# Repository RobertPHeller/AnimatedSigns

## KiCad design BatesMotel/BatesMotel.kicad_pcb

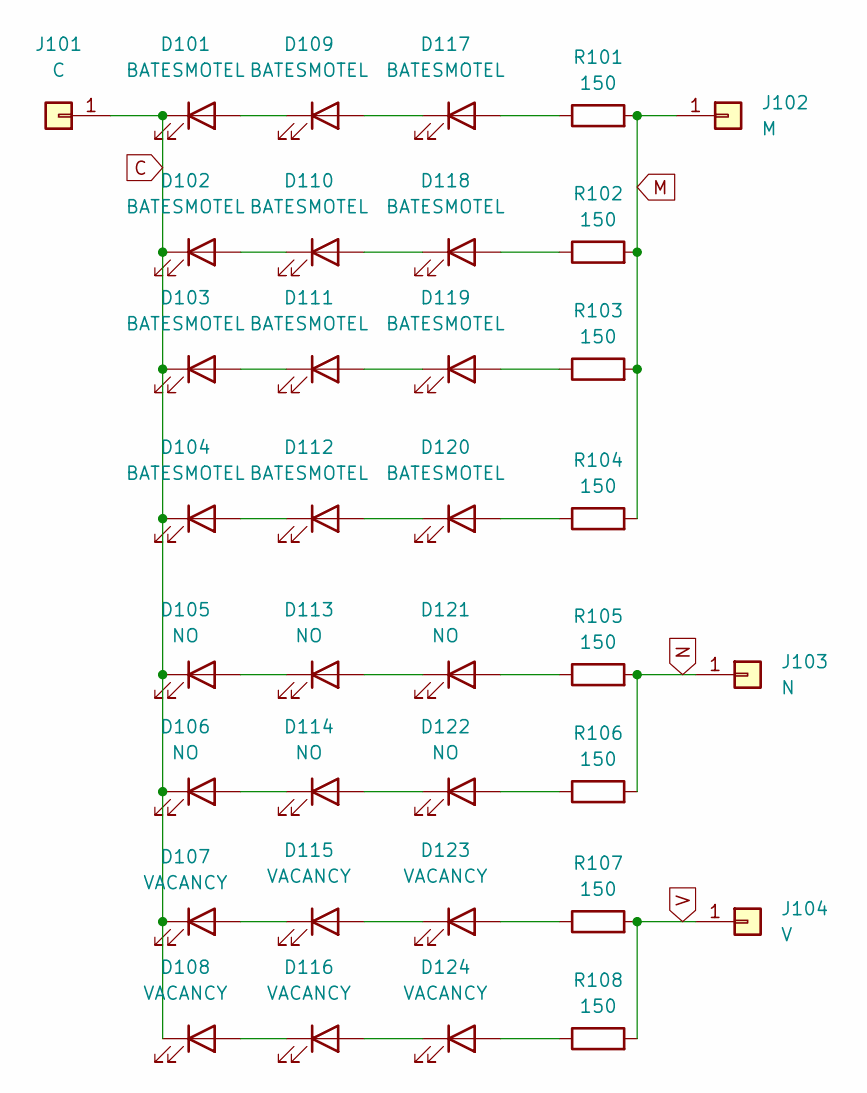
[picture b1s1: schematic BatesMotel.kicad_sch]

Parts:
D101, D102, D103, D104, D109, D110, D111, D112, D117, D118, D119, D120: BATESMOTEL; LED_1206_3216Metric; Mouser Part Number 743-S126AT5UW
D105, D106, D113, D114, D121, D122: NO; LED_0603_1608Metric; Mouser Part Number 630-HSMW-C191-U0000
D107, D108, D115, D116, D123, D124: VACANCY; LED_0603_1608Metric; Mouser Part Number 630-HSMW-C191-U0000
J101: C; ContactPad
J102: M; ContactPad
J103: N; ContactPad
J104: V; ContactPad
R101, R102, R103, R104, R105, R106, R107, R108: 150; R_0603_1608Metric; Mouser Part Number 603-RT0603FRE13150RL

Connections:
C: D101.1 (K), D102.1 (K), D103.1 (K), D104.1 (K), D105.1 (K), D106.1 (K), D107.1 (K), D108.1 (K), J101.1
M: J102.1, R101.2, R102.2, R103.2, R104.2
N: J103.1, R105.2, R106.2
unnamed: D101.2 (A), D109.1 (K)
unnamed: D102.2 (A), D110.1 (K)
unnamed: D103.2 (A), D111.1 (K)
unnamed: D104.2 (A), D112.1 (K)
unnamed: D105.2 (A), D113.1 (K)
unnamed: D106.2 (A), D114.1 (K)
unnamed: D107.2 (A), D115.1 (K)
unnamed: D108.2 (A), D116.1 (K)
unnamed: D109.2 (A), D117.1 (K)
unnamed: D110.2 (A), D118.1 (K)
unnamed: D111.2 (A), D119.1 (K)
unnamed: D112.2 (A), D120.1 (K)
unnamed: D113.2 (A), D121.1 (K)
unnamed: D114.2 (A), D122.1 (K)
unnamed: D115.2 (A), D123.1 (K)
unnamed: D116.2 (A), D124.1 (K)
unnamed: D117.2 (A), R101.1
unnamed: D118.2 (A), R102.1
unnamed: D119.2 (A), R103.1
unnamed: D120.2 (A), R104.1
unnamed: D121.2 (A), R105.1
unnamed: D122.2 (A), R106.1
unnamed: D123.2 (A), R107.1
unnamed: D124.2 (A), R108.1
V: J104.1, R107.2, R108.2

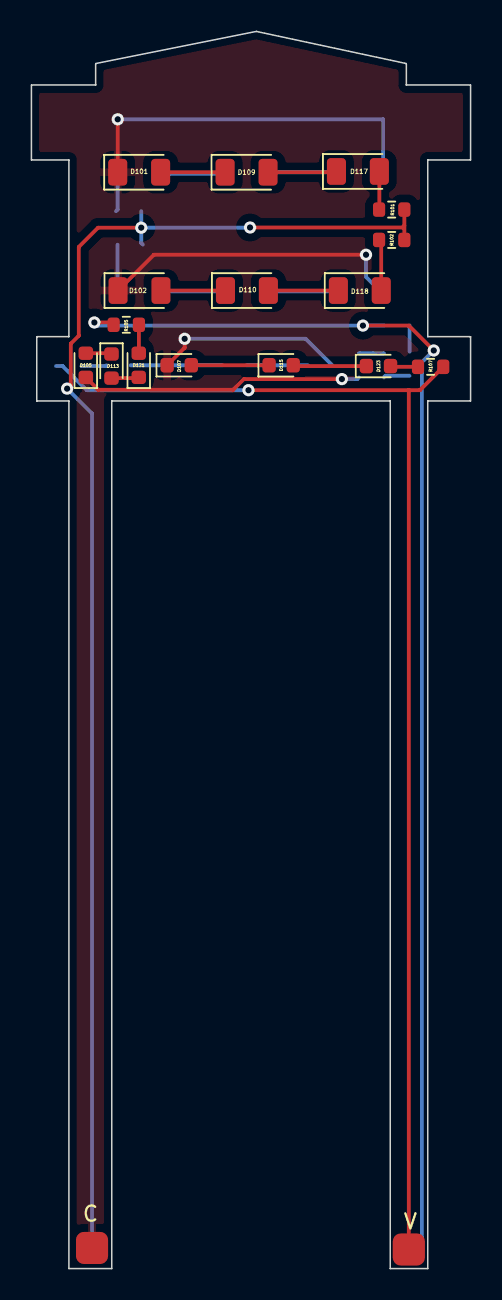
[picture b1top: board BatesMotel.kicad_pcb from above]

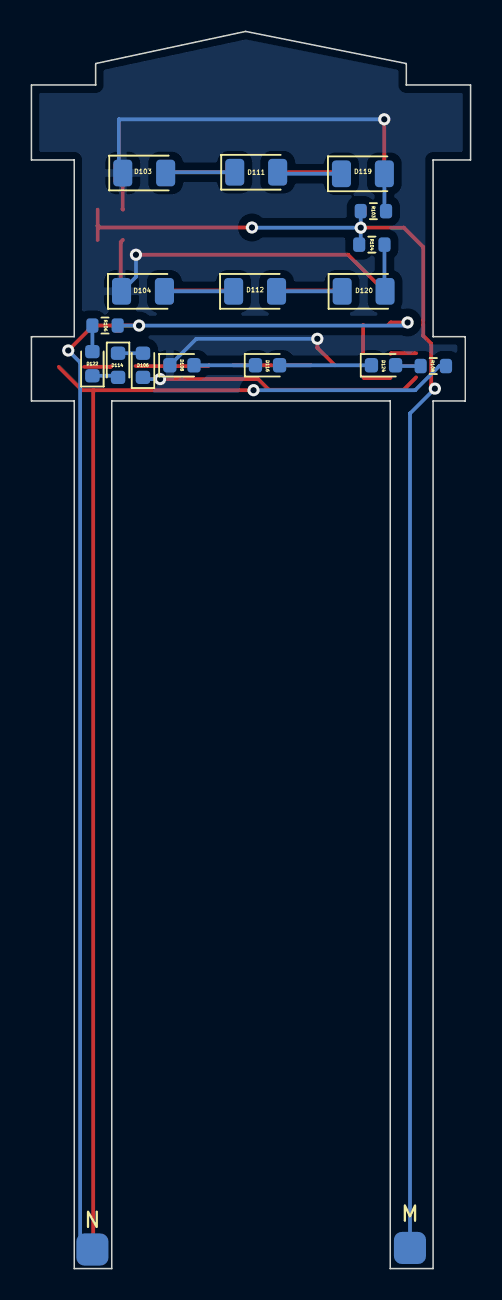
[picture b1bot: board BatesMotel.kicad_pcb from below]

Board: 2 copper layers, 28.7 x 80.7 mm, 36 parts (18 on the bottom side), 28 nets.

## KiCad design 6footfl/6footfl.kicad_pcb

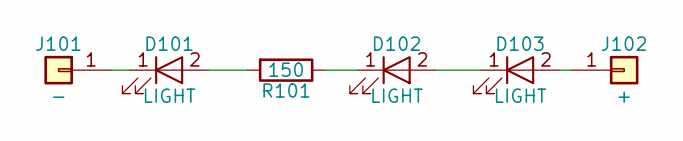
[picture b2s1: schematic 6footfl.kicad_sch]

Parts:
D101, D102, D103: LIGHT; LED_0603; Mouser Part Number 630-HSMW-C191-U0000
J101: -; SmallPad
J102: +; SmallPad
R101: 150; R_0603; Mouser Part Number 603-RT0603FRE13150RL

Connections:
unnamed: D101.1 (K), J101.1
unnamed: D101.2 (A), R101.2
unnamed: D102.1 (K), R101.1
unnamed: D102.2 (A), D103.1 (K)
unnamed: D103.2 (A), J102.1

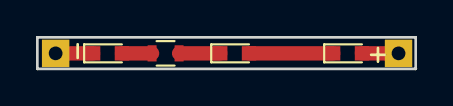
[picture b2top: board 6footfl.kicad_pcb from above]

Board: 2 copper layers, 21.0 x 1.8 mm, 6 parts (0 on the bottom side), 5 nets.

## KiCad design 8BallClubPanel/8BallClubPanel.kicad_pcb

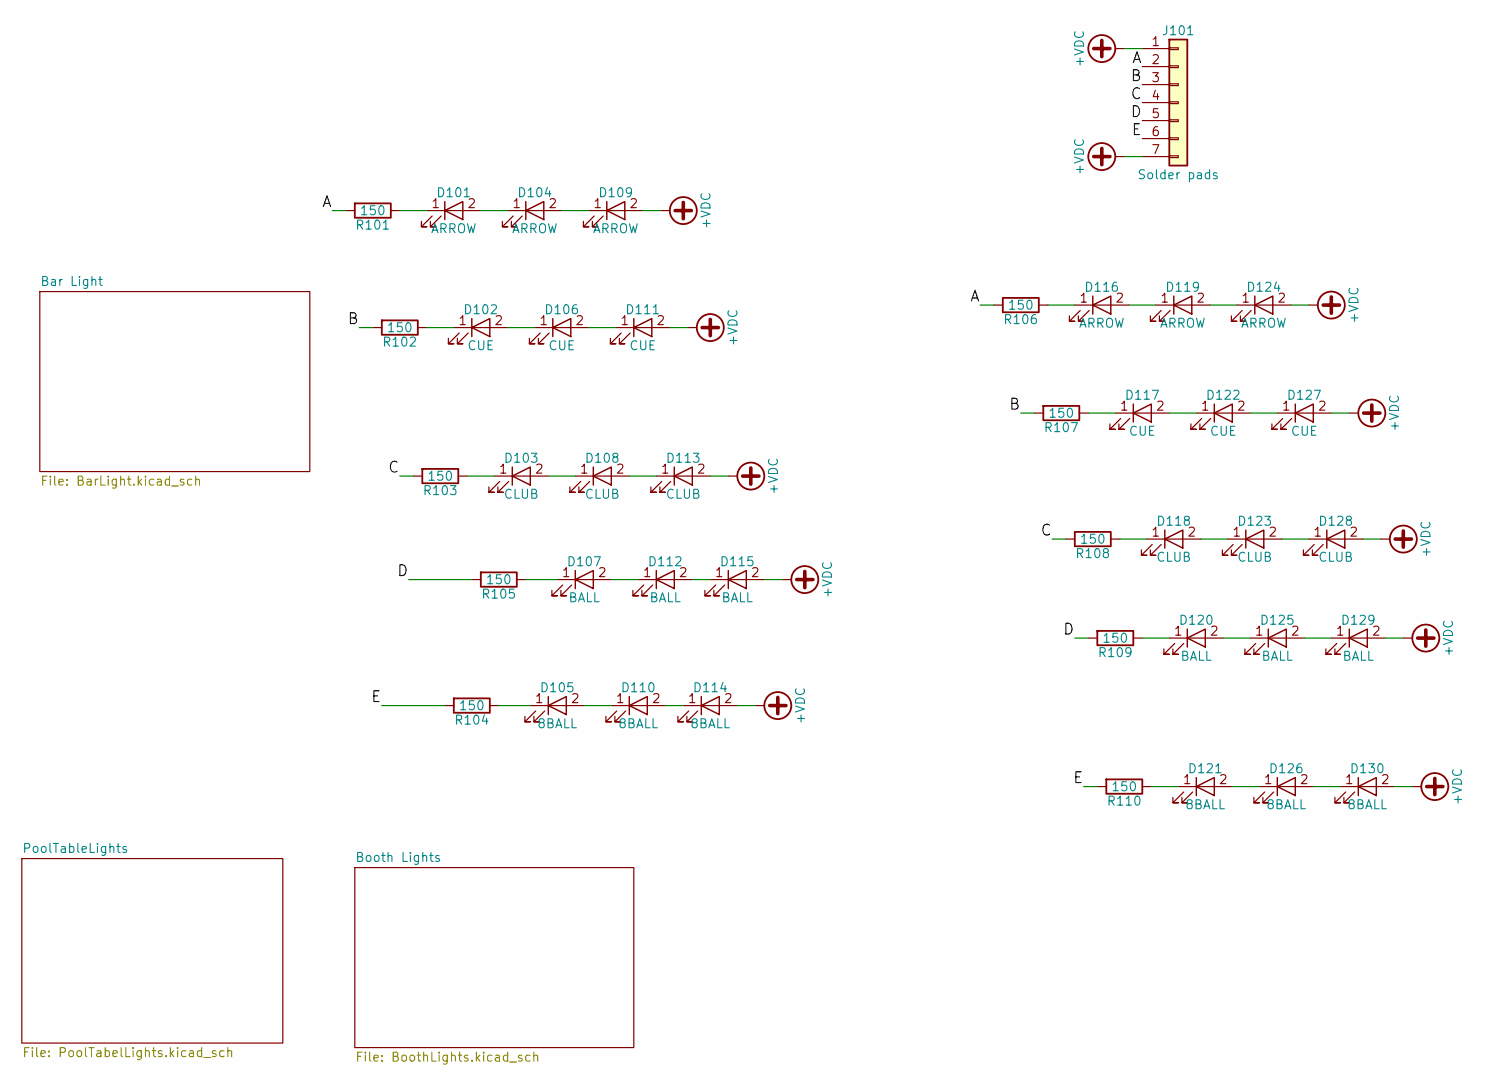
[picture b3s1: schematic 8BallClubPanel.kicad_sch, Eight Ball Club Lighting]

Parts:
D101, D104, D109, D116, D119, D124: ARROW; LED_1206_3216Metric; Mouser Part Number 743-S126AT5UW
D102, D106, D111, D117, D122, D127: CUE; LED_1206_3216Metric; Mouser Part Number 743-S126AT5UW
D103, D108, D113, D118, D123, D128: CLUB; LED_1206_3216Metric; Mouser Part Number 743-S126AT5UW
D105, D110, D114, D121, D126, D130: 8BALL; LED_1206_3216Metric; Mouser Part Number 743-S126AT5UW
D107, D112, D115, D120, D125, D129: BALL; LED_1206_3216Metric; Mouser Part Number 743-S126AT5UW
J101: Solder pads; PowerPlus5X2
R101, R102, R103, R104, R105, R106, R107, R108, R109, R110: 150; R_0603_1608Metric; Mouser Part Number 603-RT0603FRE13150RL

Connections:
+VDC: D109.2 (A), D111.2 (A), D113.2 (A), D114.2 (A), D115.2 (A), D124.2 (A), D127.2 (A), D128.2 (A), D129.2 (A), D130.2 (A), J101.1, J101.7
/A: J101.2, R101.2, R106.2
/B: J101.3, R102.2, R107.2
/C: J101.4, R103.2, R108.2
/D: J101.5, R105.2, R109.2
/E: J101.6, R104.2, R110.2
unnamed: D101.1 (K), R101.1
unnamed: D101.2 (A), D104.1 (K)
unnamed: D102.1 (K), R102.1
unnamed: D102.2 (A), D106.1 (K)
unnamed: D103.1 (K), R103.1
unnamed: D103.2 (A), D108.1 (K)
unnamed: D104.2 (A), D109.1 (K)
unnamed: D105.1 (K), R104.1
unnamed: D105.2 (A), D110.1 (K)
unnamed: D106.2 (A), D111.1 (K)
unnamed: D107.1 (K), R105.1
unnamed: D107.2 (A), D112.1 (K)
unnamed: D108.2 (A), D113.1 (K)
unnamed: D110.2 (A), D114.1 (K)
unnamed: D112.2 (A), D115.1 (K)
unnamed: D116.1 (K), R106.1
unnamed: D116.2 (A), D119.1 (K)
unnamed: D117.1 (K), R107.1
unnamed: D117.2 (A), D122.1 (K)
unnamed: D118.1 (K), R108.1
unnamed: D118.2 (A), D123.1 (K)
unnamed: D119.2 (A), D124.1 (K)
unnamed: D120.1 (K), R109.1
unnamed: D120.2 (A), D125.1 (K)
unnamed: D121.1 (K), R110.1
unnamed: D121.2 (A), D126.1 (K)
unnamed: D122.2 (A), D127.1 (K)
unnamed: D123.2 (A), D128.1 (K)
unnamed: D125.2 (A), D129.1 (K)
unnamed: D126.2 (A), D130.1 (K)

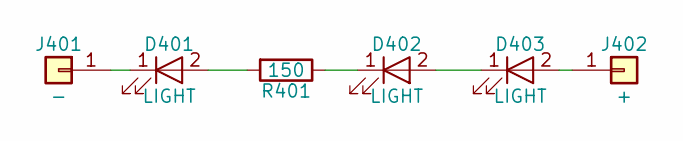
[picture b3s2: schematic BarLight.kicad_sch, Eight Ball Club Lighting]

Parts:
D401, D402, D403: LIGHT; LED_PLCC-2; Mouser Part Number 941-CLM3CWKWCWBYA153
J401: -; TestPoint_THTPad_D3.0mm_Drill1.5mm
J402: +; TestPoint_THTPad_D3.0mm_Drill1.5mm
R401: 150; R_0603_1608Metric; Mouser Part Number 603-RT0603FRE13150RL

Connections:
unnamed: D401.1 (K), J401.1
unnamed: D401.2 (A), R401.2
unnamed: D402.1 (K), R401.1
unnamed: D402.2 (A), D403.1 (K)
unnamed: D403.2 (A), J402.1

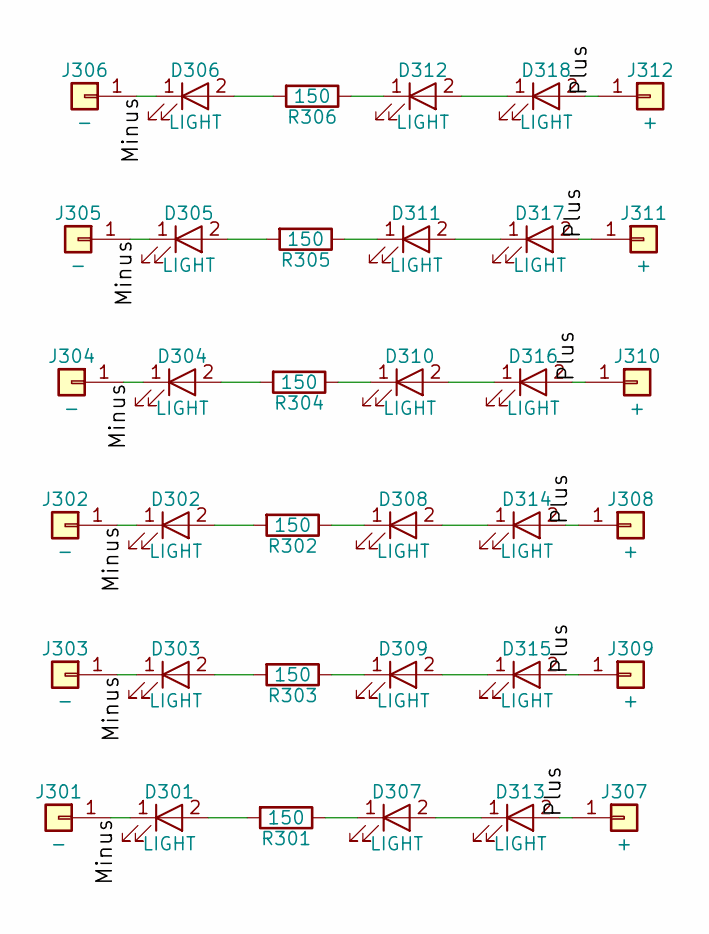
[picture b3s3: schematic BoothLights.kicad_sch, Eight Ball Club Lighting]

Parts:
D301, D302, D303, D304, D305, D306, D307, D308, D309, D310, D311, D312, D313, D314, D315, D316, D317, D318: LIGHT; LED_0402_1005Metric; Mouser Part Number 743-IN-S42ATUW
J301, J302, J303, J304, J305, J306: -; BottomPad
J307, J308, J309, J310, J311, J312: +; BottomPad
R301, R302, R303, R304, R305, R306: 150; R_0402_1005Metric; Mouser Part Number 603-RC0402JR-13150RL

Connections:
/Booth Lights/Minus: D301.1 (K), D302.1 (K), D303.1 (K), D304.1 (K), D305.1 (K), D306.1 (K), J301.1, J302.1, J303.1, J304.1, J305.1, J306.1
/Booth Lights/Plus: D313.2 (A), D314.2 (A), D315.2 (A), D316.2 (A), D317.2 (A), D318.2 (A), J307.1, J308.1, J309.1, J310.1, J311.1, J312.1
unnamed: D301.2 (A), R301.2
unnamed: D302.2 (A), R302.2
unnamed: D303.2 (A), R303.2
unnamed: D304.2 (A), R304.2
unnamed: D305.2 (A), R305.2
unnamed: D306.2 (A), R306.2
unnamed: D307.1 (K), R301.1
unnamed: D307.2 (A), D313.1 (K)
unnamed: D308.1 (K), R302.1
unnamed: D308.2 (A), D314.1 (K)
unnamed: D309.1 (K), R303.1
unnamed: D309.2 (A), D315.1 (K)
unnamed: D310.1 (K), R304.1
unnamed: D310.2 (A), D316.1 (K)
unnamed: D311.1 (K), R305.1
unnamed: D311.2 (A), D317.1 (K)
unnamed: D312.1 (K), R306.1
unnamed: D312.2 (A), D318.1 (K)

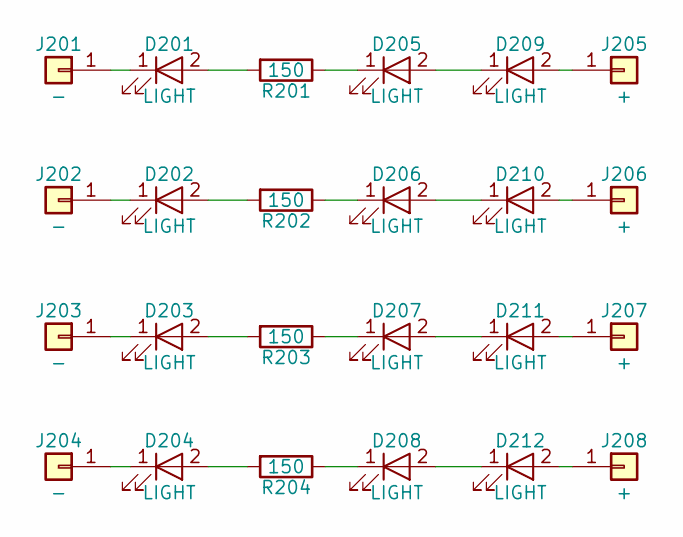
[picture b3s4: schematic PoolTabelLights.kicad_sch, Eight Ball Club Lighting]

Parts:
D201, D202, D203, D204, D205, D206, D207, D208, D209, D210, D211, D212: LIGHT; LED_0603_1608Metric; Mouser Part Number 630-HSMW-C191-U0000
J201, J202, J203, J204: -; SmallPad
J205, J206, J207, J208: +; SmallPad
R201, R202, R203, R204: 150; R_0603_1608Metric; Mouser Part Number 603-RT0603FRE13150RL

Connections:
unnamed: D201.1 (K), J201.1
unnamed: D201.2 (A), R201.2
unnamed: D202.1 (K), J202.1
unnamed: D202.2 (A), R202.2
unnamed: D203.1 (K), J203.1
unnamed: D203.2 (A), R203.2
unnamed: D204.1 (K), J204.1
unnamed: D204.2 (A), R204.2
unnamed: D205.1 (K), R201.1
unnamed: D205.2 (A), D209.1 (K)
unnamed: D206.1 (K), R202.1
unnamed: D206.2 (A), D210.1 (K)
unnamed: D207.1 (K), R203.1
unnamed: D207.2 (A), D211.1 (K)
unnamed: D208.1 (K), R204.1
unnamed: D208.2 (A), D212.1 (K)
unnamed: D209.2 (A), J205.1
unnamed: D210.2 (A), J206.1
unnamed: D211.2 (A), J207.1
unnamed: D212.2 (A), J208.1

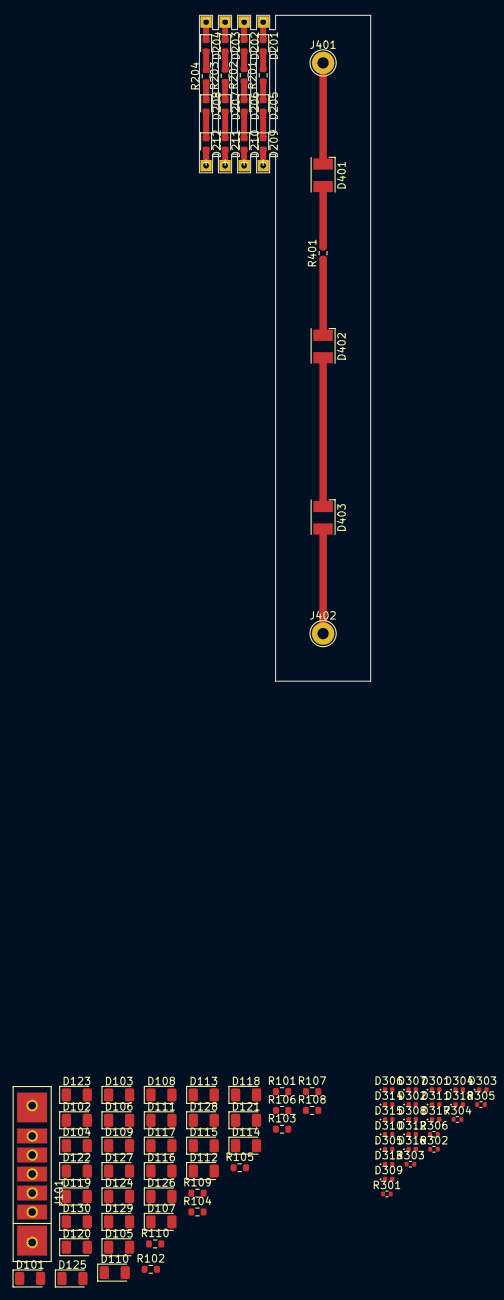
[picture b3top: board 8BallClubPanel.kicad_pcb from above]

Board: 2 copper layers, 22.9 x 88.9 mm, 107 parts (0 on the bottom side), 81 nets.

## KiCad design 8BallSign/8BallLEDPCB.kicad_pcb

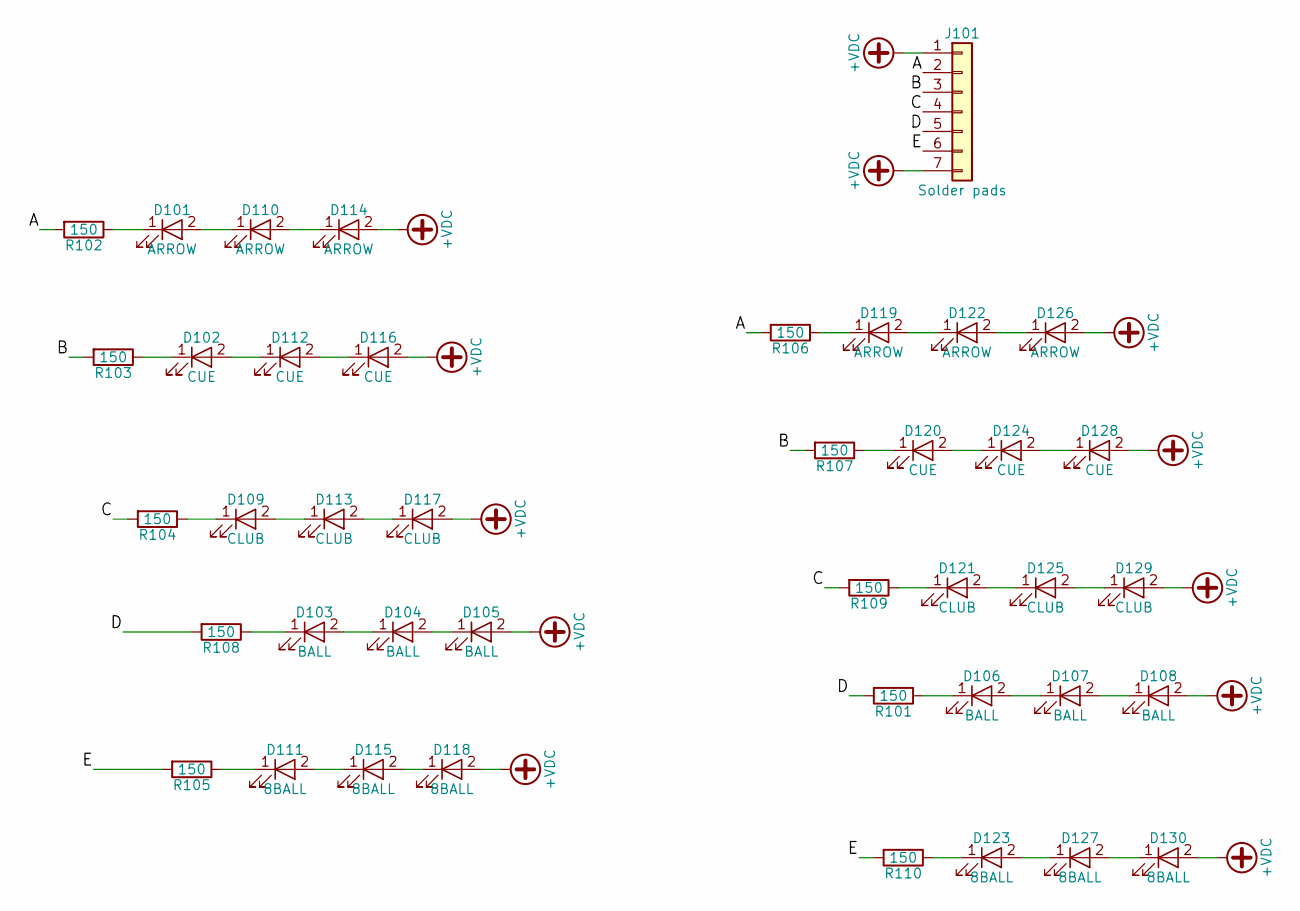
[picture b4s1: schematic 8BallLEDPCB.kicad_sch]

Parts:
D101, D110, D114, D119, D122, D126: ARROW; LED_1206; Mouser Part Number 743-S126AT5UW
D102, D112, D116, D120, D124, D128: CUE; LED_1206; Mouser Part Number 743-S126AT5UW
D103, D104, D105, D106, D107, D108: BALL; LED_1206; Mouser Part Number 743-S126AT5UW
D109, D113, D117, D121, D125, D129: CLUB; LED_1206; Mouser Part Number 743-S126AT5UW
D111, D115, D118, D123, D127, D130: 8BALL; LED_1206; Mouser Part Number 743-S126AT5UW
J101: Solder pads; PowerPlus5X2
R101, R102, R103, R104, R105, R106, R107, R108, R109, R110: 150; R_0603; Mouser Part Number 603-RT0603FRE13150RL

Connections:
+VDC: D105.2 (A), D108.2 (A), D114.2 (A), D116.2 (A), D117.2 (A), D118.2 (A), D126.2 (A), D128.2 (A), D129.2 (A), D130.2 (A), J101.1, J101.7
/A: J101.2, R102.2, R106.2
/B: J101.3, R103.2, R107.2
/C: J101.4, R104.2, R109.2
/D: J101.5, R101.2, R108.2
/E: J101.6, R105.2, R110.2
unnamed: D101.1 (K), R102.1
unnamed: D101.2 (A), D110.1 (K)
unnamed: D102.1 (K), R103.1
unnamed: D102.2 (A), D112.1 (K)
unnamed: D103.1 (K), R108.1
unnamed: D103.2 (A), D104.1 (K)
unnamed: D104.2 (A), D105.1 (K)
unnamed: D106.1 (K), R101.1
unnamed: D106.2 (A), D107.1 (K)
unnamed: D107.2 (A), D108.1 (K)
unnamed: D109.1 (K), R104.1
unnamed: D109.2 (A), D113.1 (K)
unnamed: D110.2 (A), D114.1 (K)
unnamed: D111.1 (K), R105.1
unnamed: D111.2 (A), D115.1 (K)
unnamed: D112.2 (A), D116.1 (K)
unnamed: D113.2 (A), D117.1 (K)
unnamed: D115.2 (A), D118.1 (K)
unnamed: D119.1 (K), R106.1
unnamed: D119.2 (A), D122.1 (K)
unnamed: D120.1 (K), R107.1
unnamed: D120.2 (A), D124.1 (K)
unnamed: D121.1 (K), R109.1
unnamed: D121.2 (A), D125.1 (K)
unnamed: D122.2 (A), D126.1 (K)
unnamed: D123.1 (K), R110.1
unnamed: D123.2 (A), D127.1 (K)
unnamed: D124.2 (A), D128.1 (K)
unnamed: D125.2 (A), D129.1 (K)
unnamed: D127.2 (A), D130.1 (K)

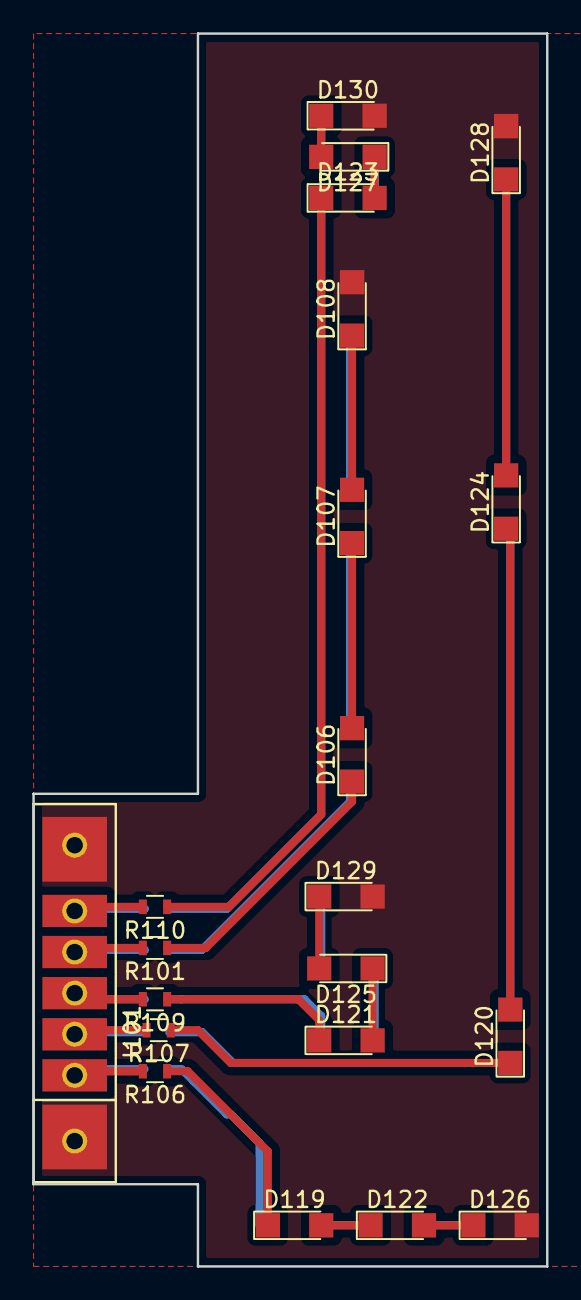
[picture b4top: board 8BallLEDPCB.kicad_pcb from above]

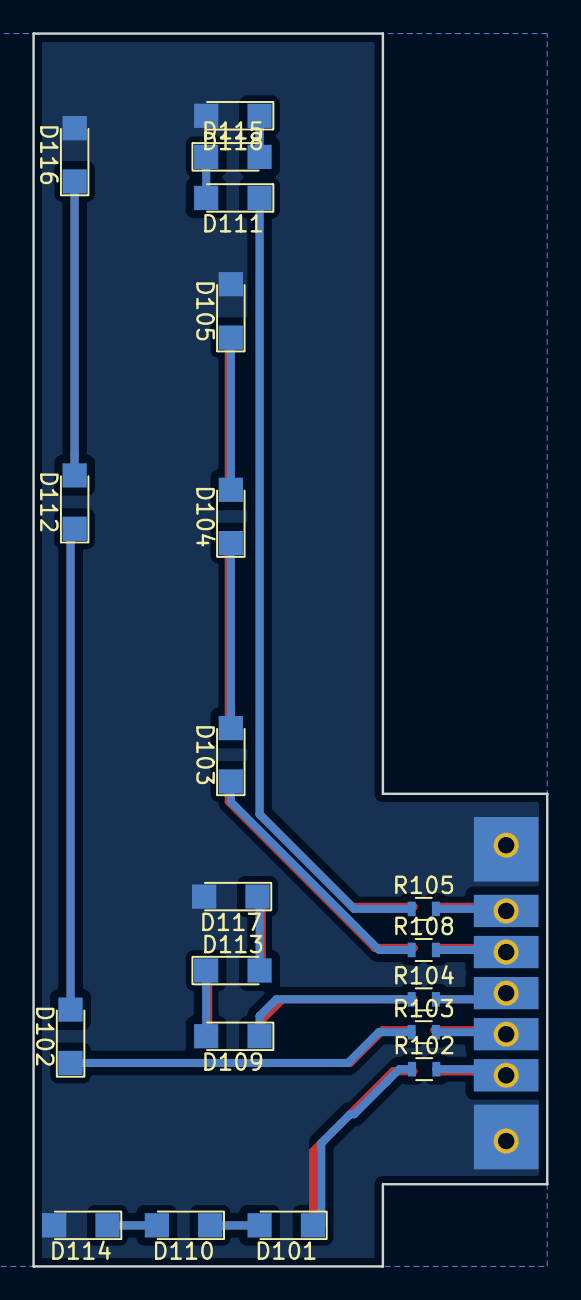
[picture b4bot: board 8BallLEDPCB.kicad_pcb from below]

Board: 2 copper layers, 31.8 x 76.2 mm, 41 parts (20 on the bottom side), 36 nets.

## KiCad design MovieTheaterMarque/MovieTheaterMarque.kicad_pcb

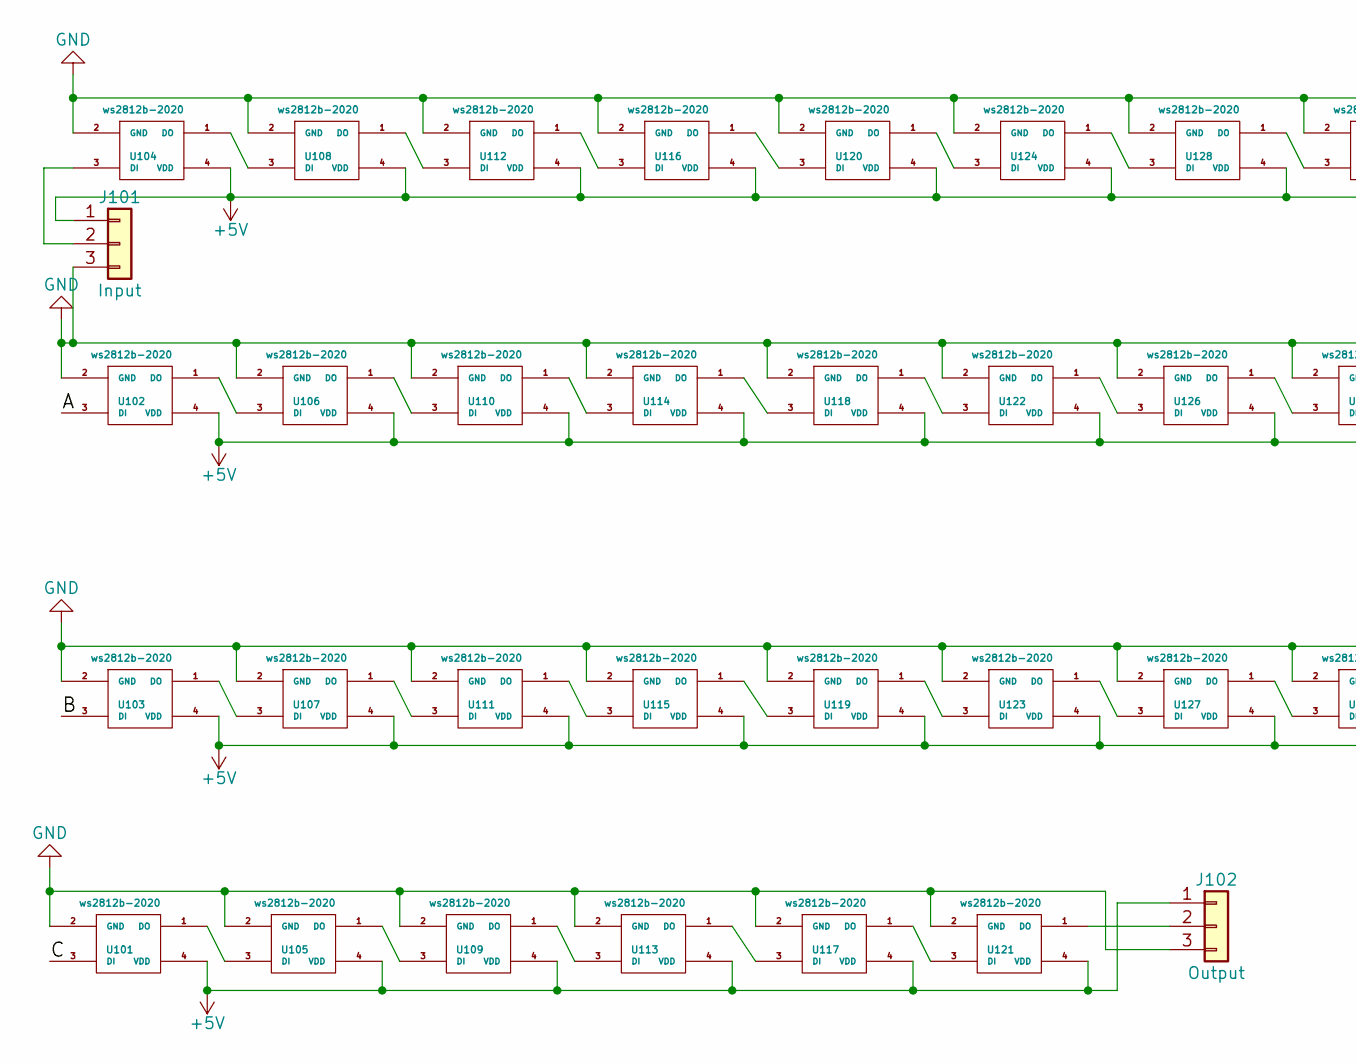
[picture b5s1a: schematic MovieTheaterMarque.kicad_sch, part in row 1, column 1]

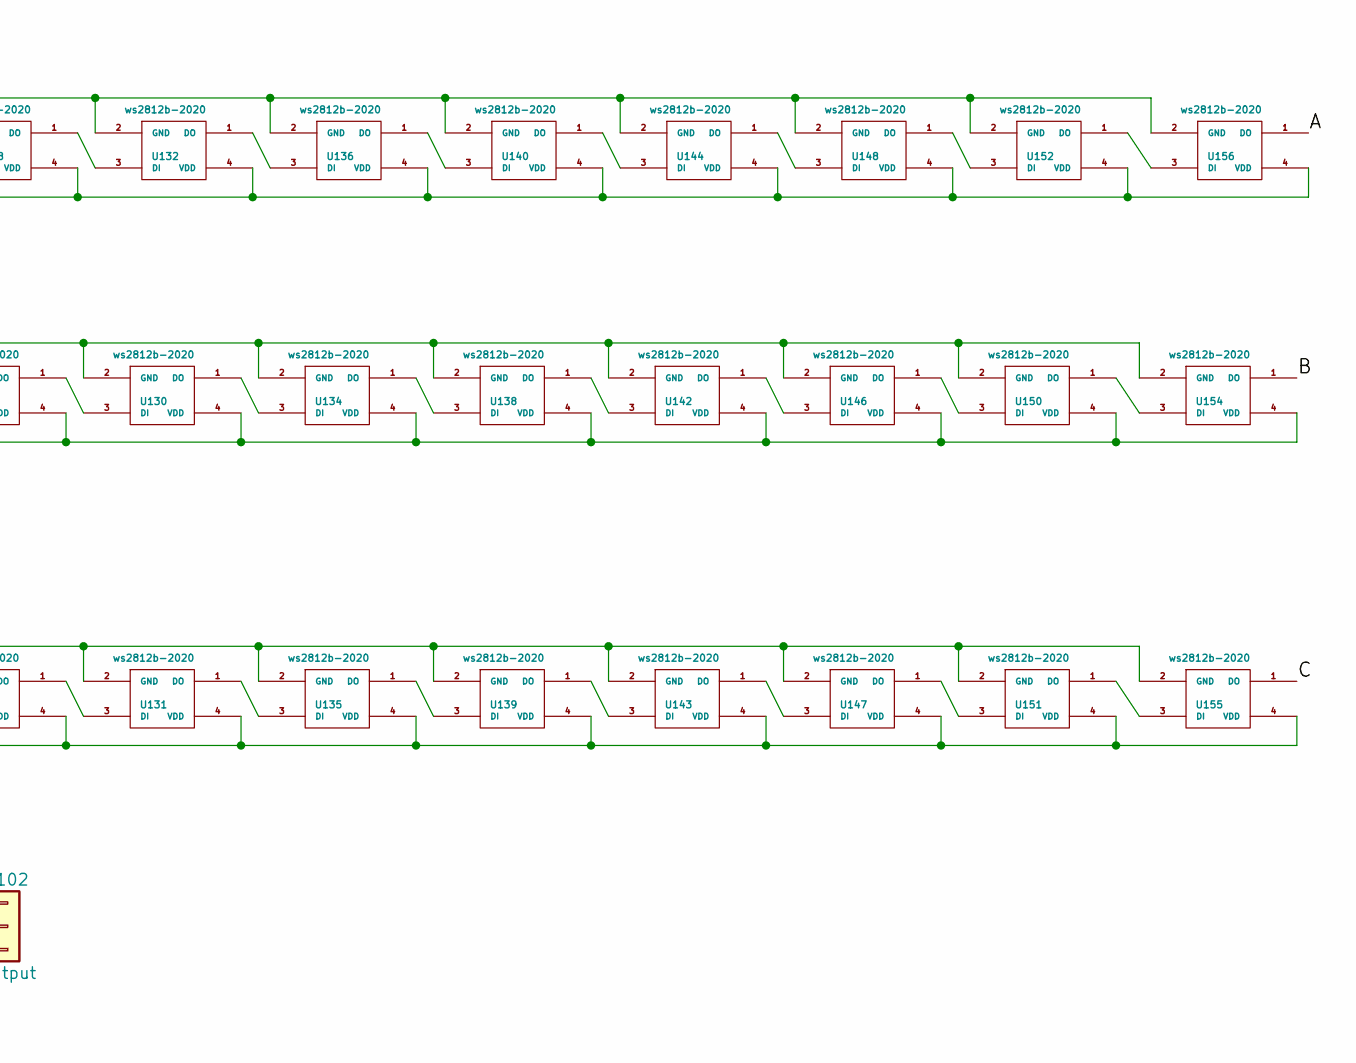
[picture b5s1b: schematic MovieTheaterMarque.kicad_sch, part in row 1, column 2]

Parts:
J101: Input; SolderWirePad_3x_0-8mmDrill
J102: Output; SolderWirePad_3x_0-8mmDrill
U101, U102, U103, U104, U105, U106, U107, U108, U109, U110, U111, U112, U113, U114, U115, U116, U117, U118, U119, U120, U121, U122, U123, U124, U126, U127, U128, U130, U131, U132, U134, U135, U136, U138, U139, U140, U142, U143, U144, U146, U147, U148, U150, U151, U152, U154, U155, U156: ws2812b-2020; ws2812B-2020-4

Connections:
+5V: J101.1, J102.1, U101.4 (VDD), U102.4 (VDD), U103.4 (VDD), U104.4 (VDD), U105.4 (VDD), U106.4 (VDD), U107.4 (VDD), U108.4 (VDD), U109.4 (VDD), U110.4 (VDD), U111.4 (VDD), U112.4 (VDD), U113.4 (VDD), U114.4 (VDD), U115.4 (VDD), U116.4 (VDD), U117.4 (VDD), U118.4 (VDD), U119.4 (VDD), U120.4 (VDD), U121.4 (VDD), U122.4 (VDD), U123.4 (VDD), U124.4 (VDD), U126.4 (VDD), U127.4 (VDD), U128.4 (VDD), U130.4 (VDD), U131.4 (VDD), U132.4 (VDD), U134.4 (VDD), U135.4 (VDD), U136.4 (VDD), U138.4 (VDD), U139.4 (VDD), U140.4 (VDD), U142.4 (VDD), U143.4 (VDD), U144.4 (VDD), U146.4 (VDD), U147.4 (VDD), U148.4 (VDD), U150.4 (VDD), U151.4 (VDD), U152.4 (VDD), U154.4 (VDD), U155.4 (VDD), U156.4 (VDD)
/A: U102.3 (DI), U156.1 (DO)
/B: U103.3 (DI), U154.1 (DO)
/C: U101.3 (DI), U155.1 (DO)
GND: J101.3, J102.3, U101.2 (GND), U102.2 (GND), U103.2 (GND), U104.2 (GND), U105.2 (GND), U106.2 (GND), U107.2 (GND), U108.2 (GND), U109.2 (GND), U110.2 (GND), U111.2 (GND), U112.2 (GND), U113.2 (GND), U114.2 (GND), U115.2 (GND), U116.2 (GND), U117.2 (GND), U118.2 (GND), U119.2 (GND), U120.2 (GND), U121.2 (GND), U122.2 (GND), U123.2 (GND), U124.2 (GND), U126.2 (GND), U127.2 (GND), U128.2 (GND), U130.2 (GND), U131.2 (GND), U132.2 (GND), U134.2 (GND), U135.2 (GND), U136.2 (GND), U138.2 (GND), U139.2 (GND), U140.2 (GND), U142.2 (GND), U143.2 (GND), U144.2 (GND), U146.2 (GND), U147.2 (GND), U148.2 (GND), U150.2 (GND), U151.2 (GND), U152.2 (GND), U154.2 (GND), U155.2 (GND), U156.2 (GND)
unnamed: J101.2, U104.3 (DI)
unnamed: J102.2, U121.1 (DO)
unnamed: U101.1 (DO), U105.3 (DI)
unnamed: U102.1 (DO), U106.3 (DI)
unnamed: U103.1 (DO), U107.3 (DI)
unnamed: U104.1 (DO), U108.3 (DI)
unnamed: U105.1 (DO), U109.3 (DI)
unnamed: U106.1 (DO), U110.3 (DI)
unnamed: U107.1 (DO), U111.3 (DI)
unnamed: U108.1 (DO), U112.3 (DI)
unnamed: U109.1 (DO), U113.3 (DI)
unnamed: U110.1 (DO), U114.3 (DI)
unnamed: U111.1 (DO), U115.3 (DI)
unnamed: U112.1 (DO), U116.3 (DI)
unnamed: U113.1 (DO), U117.3 (DI)
unnamed: U114.1 (DO), U118.3 (DI)
unnamed: U115.1 (DO), U119.3 (DI)
unnamed: U116.1 (DO), U120.3 (DI)
unnamed: U117.1 (DO), U121.3 (DI)
unnamed: U118.1 (DO), U122.3 (DI)
unnamed: U119.1 (DO), U123.3 (DI)
unnamed: U120.1 (DO), U124.3 (DI)
unnamed: U122.1 (DO), U126.3 (DI)
unnamed: U123.1 (DO), U127.3 (DI)
unnamed: U124.1 (DO), U128.3 (DI)
unnamed: U126.1 (DO), U130.3 (DI)
unnamed: U127.1 (DO), U131.3 (DI)
unnamed: U128.1 (DO), U132.3 (DI)
unnamed: U130.1 (DO), U134.3 (DI)
unnamed: U131.1 (DO), U135.3 (DI)
unnamed: U132.1 (DO), U136.3 (DI)
unnamed: U134.1 (DO), U138.3 (DI)
unnamed: U135.1 (DO), U139.3 (DI)
unnamed: U136.1 (DO), U140.3 (DI)
unnamed: U138.1 (DO), U142.3 (DI)
unnamed: U139.1 (DO), U143.3 (DI)
unnamed: U140.1 (DO), U144.3 (DI)
unnamed: U142.1 (DO), U146.3 (DI)
unnamed: U143.1 (DO), U147.3 (DI)
unnamed: U144.1 (DO), U148.3 (DI)
unnamed: U146.1 (DO), U150.3 (DI)
unnamed: U147.1 (DO), U151.3 (DI)
unnamed: U148.1 (DO), U152.3 (DI)
unnamed: U150.1 (DO), U154.3 (DI)
unnamed: U151.1 (DO), U155.3 (DI)
unnamed: U152.1 (DO), U156.3 (DI)

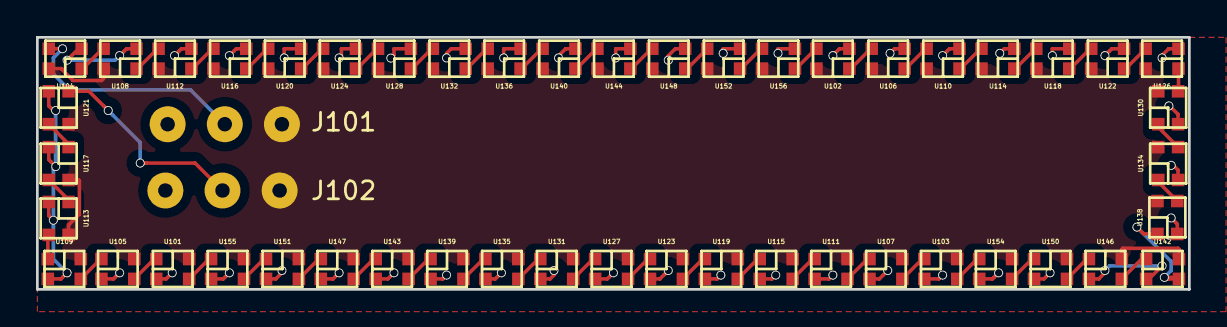
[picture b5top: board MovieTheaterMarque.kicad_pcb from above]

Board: 2 copper layers, 64.0 x 14.0 mm, 50 parts (0 on the bottom side), 51 nets.

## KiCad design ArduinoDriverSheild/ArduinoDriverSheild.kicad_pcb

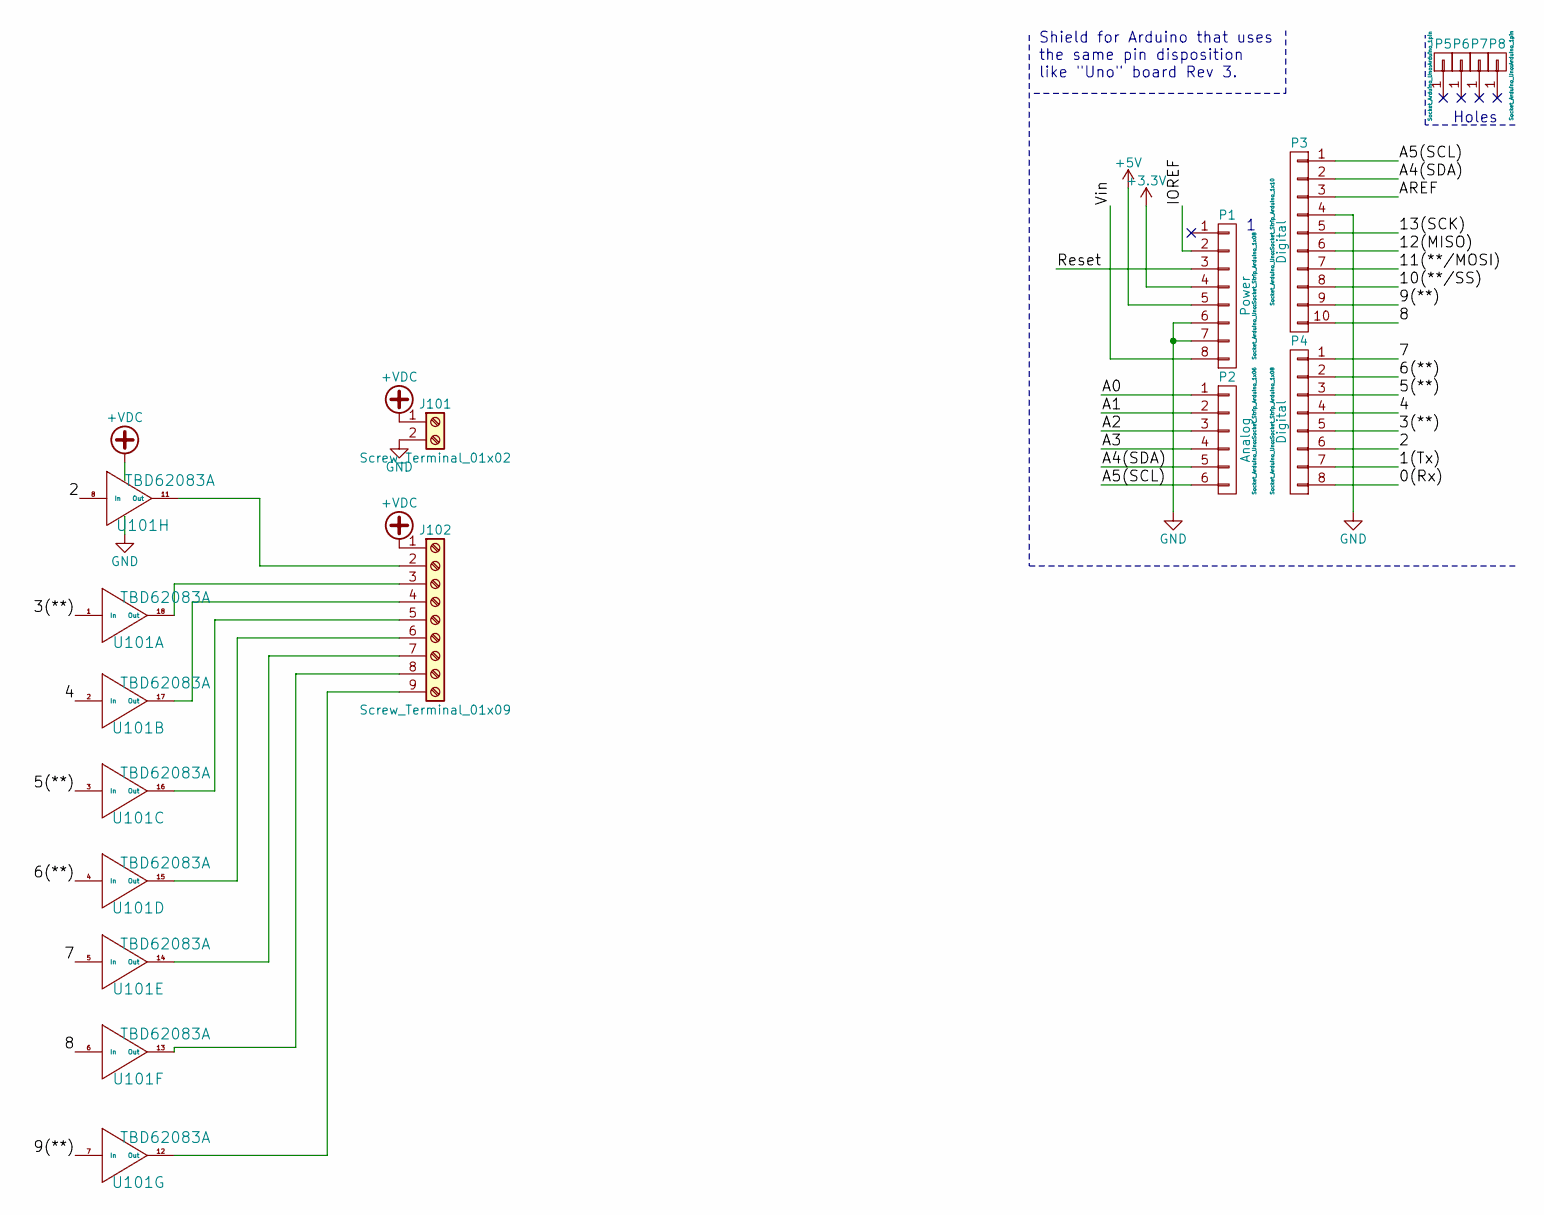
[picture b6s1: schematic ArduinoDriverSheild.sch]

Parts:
J101: Screw_Terminal_01x02; TerminalBlock_Pheonix_PT-3.5mm_2pol
J102: Screw_Terminal_01x09; TerminalBlock_Pheonix_PT-3.5mm_9pol
P1: Power; Socket_Strip_Arduino_1x08
P2: Analog; Socket_Strip_Arduino_1x06
P3: Digital; Socket_Strip_Arduino_1x10
P4: Digital; Socket_Strip_Arduino_1x08
P5, P6, P7, P8: CONN_01X01; Arduino_1pin
U101: TBD62083A; SOIC-18W_7.5x11.6mm_Pitch1.27mm

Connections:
+3V3: P1.4
+5V: P1.5
+VDC: J101.1, J102.1, U101.10 (OC)
/0(Rx): P4.8
/1(Tx): P4.7
/2: P4.6, U101.8 (In)
/3(**): P4.5, U101.1 (In)
/4: P4.4, U101.2 (In)
/5(**): P4.3, U101.3 (In)
/6(**): P4.2, U101.4 (In)
/7: P4.1, U101.5 (In)
/8: P3.10, U101.6 (In)
/9(**): P3.9, U101.7 (In)
/10(**/SS): P3.8
/11(**/MOSI): P3.7
/12(MISO): P3.6
/13(SCK): P3.5
/A0: P2.1
/A1: P2.2
/A2: P2.3
/A3: P2.4
/A4(SDA): P2.5, P3.2
/A5(SCL): P2.6, P3.1
/AREF: P3.3
/IOREF: P1.2
/Reset: P1.3
/Vin: P1.8
GND: J101.2, P1.6, P1.7, P3.4, U101.9 (IC)
unnamed: J102.2, U101.11 (Out)
unnamed: J102.3, U101.18 (Out)
unnamed: J102.4, U101.17 (Out)
unnamed: J102.5, U101.16 (Out)
unnamed: J102.6, U101.15 (Out)
unnamed: J102.7, U101.14 (Out)
unnamed: J102.8, U101.13 (Out)
unnamed: J102.9, U101.12 (Out)

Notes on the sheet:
Holes
Shield for Arduino that uses the same pin disposition like "Uno" board Rev 3.
